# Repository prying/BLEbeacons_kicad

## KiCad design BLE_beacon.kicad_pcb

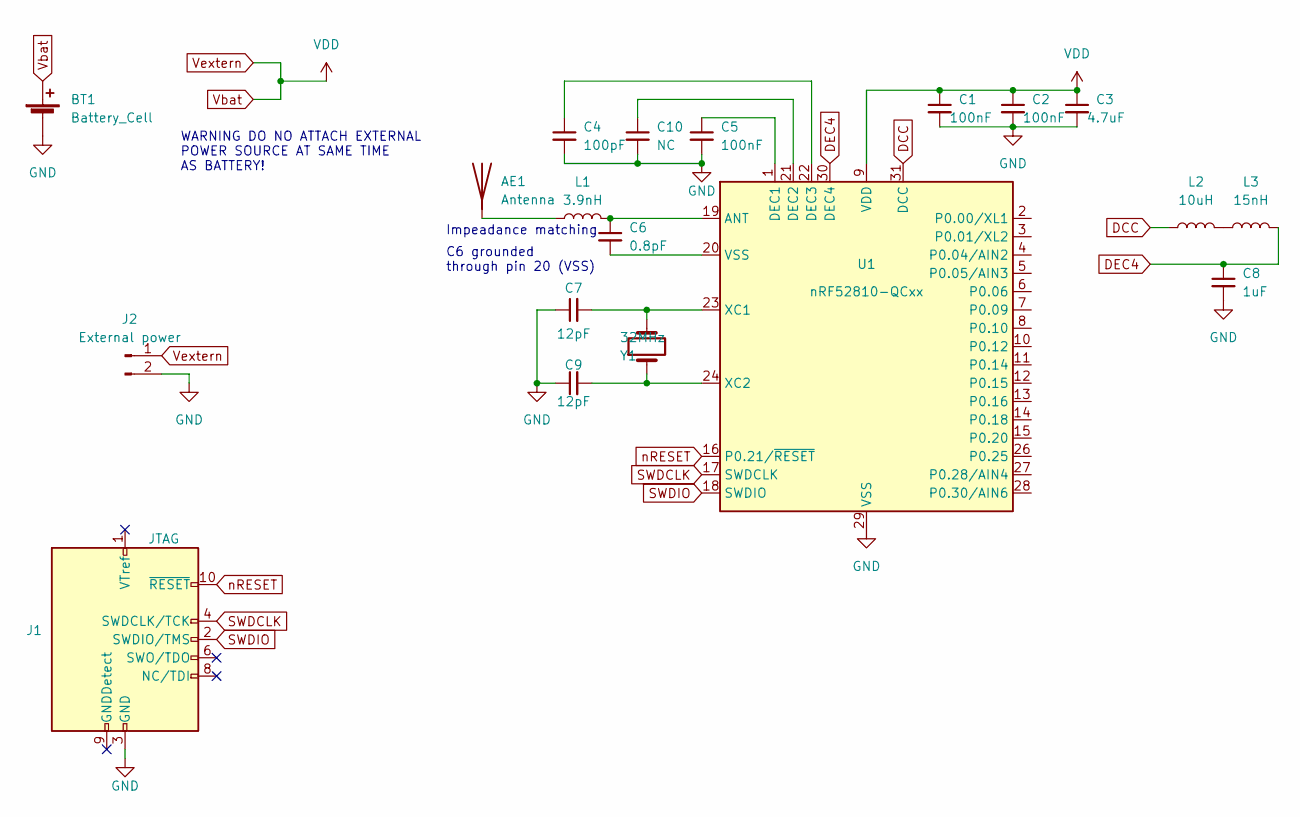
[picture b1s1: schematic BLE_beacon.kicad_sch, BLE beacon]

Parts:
AE1: Antenna; Texas_SWRA117D_2.4GHz_Left
BT1: Battery_Cell; BAT_BAT-HLD-006-SMT; MPN BAT-HLD-006-SMT
C1, C2, C5: 100nF; C_0402_1005Metric_Pad0.74x0.62mm_HandSolder; MPN CL05B104KO5NNNC
C3: 4.7uF; C_0603_1608Metric; MPN CL10A475KP8NNNC
C4: 100pF; C_0402_1005Metric_Pad0.74x0.62mm_HandSolder; MPN CL05C101JB5NNNC
C6: 0.8pF; C_0402_1005Metric_Pad0.74x0.62mm_HandSolder; MPN GCQ1555C1HR12BB01D
C7, C9: 12pF; C_0402_1005Metric_Pad0.74x0.62mm_HandSolder; MPN GRM1555C1H120GA01D
C8: 1uF; C_0603_1608Metric; MPN CL10B105KP8NNNC
C10: NC; C_0402_1005Metric_Pad0.74x0.62mm_HandSolder
J1: JTAG; PinSocket_2x05_P1.27mm_Vertical_SMD; MPN 1156861
J2: External power; PinSocket_1x02_P2.54mm_Vertical
L1: 3.9nH; L_0402_1005Metric_Pad0.77x0.64mm_HandSolder; MPN 0402HS-3N9EJTS
L2: 10uH; L_0603_1608Metric; MPN MCL1608V1-100-R
L3: 15nH; L_0402_1005Metric_Pad0.77x0.64mm_HandSolder; MPN 74478415
U1: nRF52810-QCxx; QFN-32-1EP_5x5mm_P0.5mm_EP3.6x3.6mm; MPN NRF52810-QCAA-R
Y1: 32MHz; Oscillator_SMD_ECS_2520MV-xxx-xx-4Pin_2.5x2.0mm; MPN ECS-320-8-36CKM-TR3

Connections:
DCC: L2.1, U1.31 (DCC)
DCC4: C8.1, L3.2, U1.30 (DEC4)
GND: AE1.2, BT1.2 (-), C1.2, C2.2, C3.2, C4.2, C5.2, C7.1, C8.2, C9.1, C10.2, J1.3 (GND), J1.5 (GND), J2.2, U1.29 (VSS), U1.33 (VSS)
unnamed: AE1.1 (A), L1.1
unnamed: C4.1, U1.22 (DEC3)
unnamed: C5.1, U1.1 (DEC1)
unnamed: C6.1, L1.2, U1.19 (ANT)
unnamed: C7.2, U1.23 (XC1), Y1.3
unnamed: C9.2, U1.24 (XC2), Y1.1
unnamed: C10.1, U1.21 (DEC2)
unnamed: L2.2, L3.1
unnamed: C6.2, U1.20 (VSS)
SWDCLK: J1.4 (SWDCLK/TCK), U1.17 (SWDCLK)
SWDIO: J1.2 (SWDIO/TMS), U1.18 (SWDIO)
VDD: BT1.1 (+), C1.1, C2.1, C3.1, J2.1, U1.9 (VDD), U1.25 (VDD), U1.32 (VDD)
nRESET: J1.10 (~RESET), U1.16 (P0.21/~RESET)

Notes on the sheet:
WARNING DO NO ATTACH EXTERNAL POWER SOURCE AT SAME TIME AS BATTERY!
Impeadance matching
C6 grounded through pin 20 (VSS)

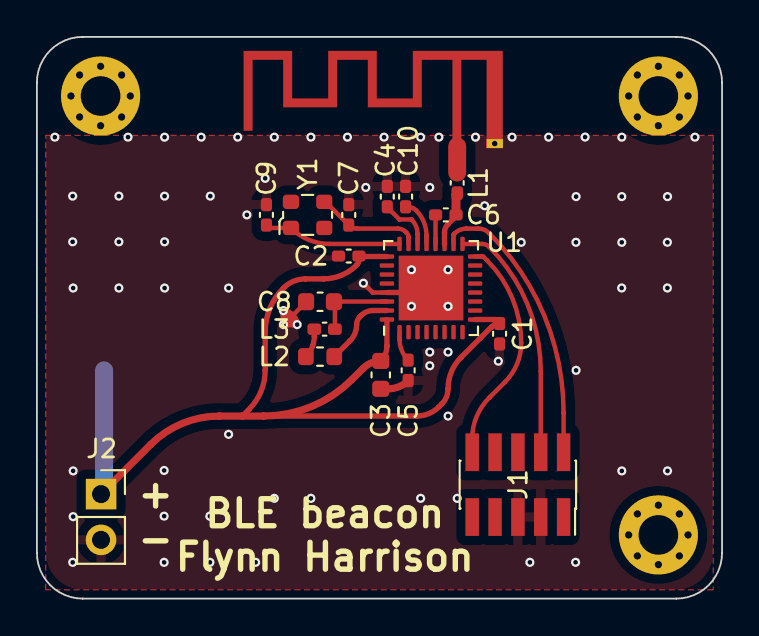
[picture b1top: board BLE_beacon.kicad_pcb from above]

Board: 2 copper layers, 38.1 x 31.2 mm, 19 parts (1 on the bottom side), 16 nets.

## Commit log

2022-05-25 inital commit
